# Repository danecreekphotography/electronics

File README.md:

# electronics
Random electronics projects

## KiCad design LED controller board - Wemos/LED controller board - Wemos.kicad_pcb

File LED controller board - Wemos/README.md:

# LED Controller Board - Wemos D1 Mini

This is a simple board that adds a logic level shifter to the D4 and RX pins
of a Wemos D1 Mini. With +5V and Ground output pins as well it makes a handy
little board for controlling short runs of LED light strips that don't require a
big external power supply.

## Schematic

A [printable version of the schematic](schematic.pdf) is available in PDF format.

## Bill of Materials

| Symbol | Description                                  | Quantity | Source                                                                                                         | Notes                                                                                                            |
| ------ | -------------------------------------------- | -------- | -------------------------------------------------------------------------------------------------------------- | ---------------------------------------------------------------------------------------------------------------- |
| C1     | 10 uF ceramic capacitor                      | 1        | [DigiKey](https://www.digikey.com/product-detail/en/tdk-corporation/FG16X7R1E106KRT06/445-173156-1-ND/5811761) | 2.5mm lead spacing                                                                                               |
| C2     | 0.1 uF ceramic capacitor                     | 1        | [DigiKey](https://www.digikey.com/product-detail/en/kemet/C322C104M5U5TA/399-4331-ND/818107)                   | 5mm lead spacing                                                                                                 |
| J1     | Molex KK male two pin right angle connector  | 1        | [DigiKey](https://www.digikey.com/product-detail/en/molex/1718570002/WM10157-ND/4423113)                       |                                                                                                                  |
| J2     | 1x8 2.54mm female pin header                 | 1        |                                                                                                                | This comes with the Wemos D1 Mini                                                                                |
| J3     | 1x8 2.54mm female pin header                 | 1        |                                                                                                                | This comes with the Wemos D1 Mini                                                                                |
| J4     | Molex KK male four pin right angle connector | 1        | [DigiKey](https://www.digikey.com/product-detail/en/molex/1718570004/WM10159-ND/4423115)                       |                                                                                                                  |
| U1     | Wemos D1 Mini                                | 1        | [Amazon](https://www.amazon.com/gp/product/B076F52NQD)                                                         | Header pins come with this set from Amazon so there is no need to buy additional headers to solder to the board. |
| U2     | TI CD40109BPWR unidirectional level shifter  | 1        | [DigiKey](https://www.digikey.com/product-detail/en/texas-instruments/CD40109BPWR/296-12163-1-ND/412005)       |                                                                                                                  |

## Ordering the PCB

The PCB can easily be [ordered from PCBWay](https://www.pcbway.com/project/shareproject/LED_Controller_Board___Wemos_D1_Mini.html). They're cheap, great quality, and arrive quickly. The default settings PCBWay applies to the board are perfect. All you have to
do is pick your favourite solder mask colour!

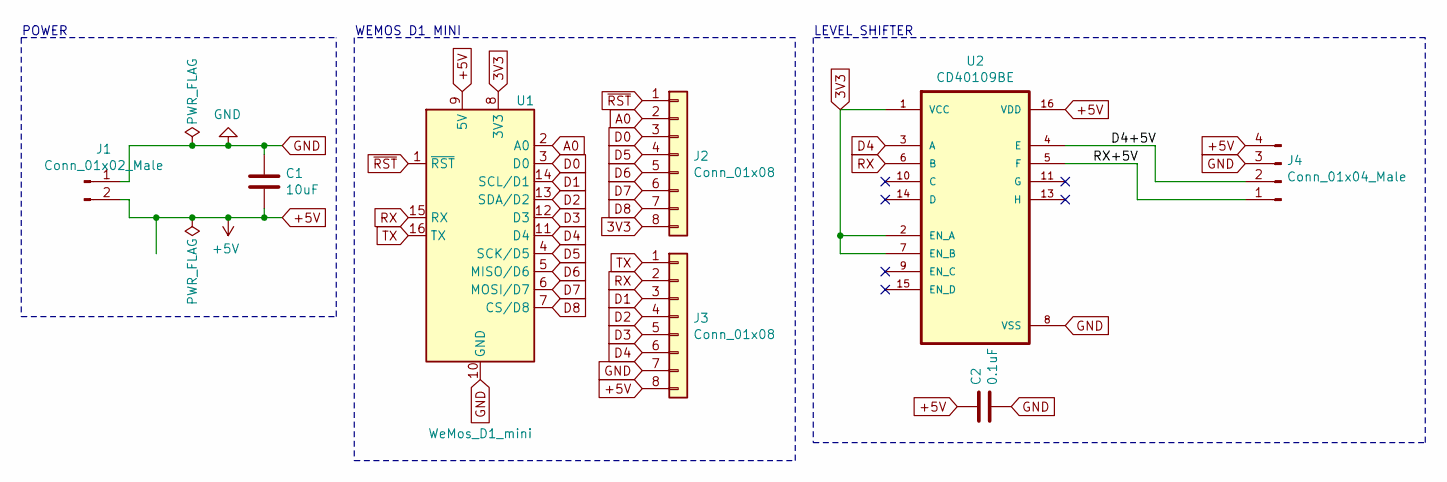
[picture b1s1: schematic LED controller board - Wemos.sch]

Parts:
C1: 10uF; C_Disc_D5.0mm_W2.5mm_P2.50mm
C2: 0.1uF; C_Disc_D5.0mm_W2.5mm_P5.00mm
J1: Conn_01x02_Male; Molex_KK-254_AE-6410-02A_1x02_P2.54mm_Horizontal
J2, J3: Conn_01x08; PinHeader_1x08_P2.54mm_Vertical
J4: Conn_01x04_Male; Molex_KK-254_AE-6410-04A_1x04_P2.54mm_Horizontal
U1: WeMos_D1_mini; WEMOS_D1_mini_light
U2: CD40109BE; 16TSSOP

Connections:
3V3: J2.8, U1.8 (3V3), U2.1 (VCC), U2.2 (EN_A), U2.7 (EN_B)
+5V: C1.2, C2.1, J1.2, J3.8, J4.4, U1.9 (5V), U2.16 (VDD)
/D4+5V: J4.2, U2.4 (E)
/RX+5V: J4.1, U2.5 (F)
A0: J2.2, U1.2 (A0)
D0: J2.3, U1.3 (D0)
D1: J3.3, U1.14 (SCL/D1)
D2: J3.4, U1.13 (SDA/D2)
D3: J3.5, U1.12 (D3)
D4: J3.6, U1.11 (D4), U2.3 (A)
D5: J2.4, U1.4 (SCK/D5)
D6: J2.5, U1.5 (MISO/D6)
D7: J2.6, U1.6 (MOSI/D7)
D8: J2.7, U1.7 (CS/D8)
GND: C1.1, C2.2, J1.1, J3.7, J4.3, U1.10 (GND), U2.8 (VSS)
RX: J3.2, U1.15 (RX), U2.6 (B)
TX: J3.1, U1.16 (TX)
~RST: J2.1, U1.1 (~RST)

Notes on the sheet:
POWER
WEMOS D1 MINI
LEVEL SHIFTER

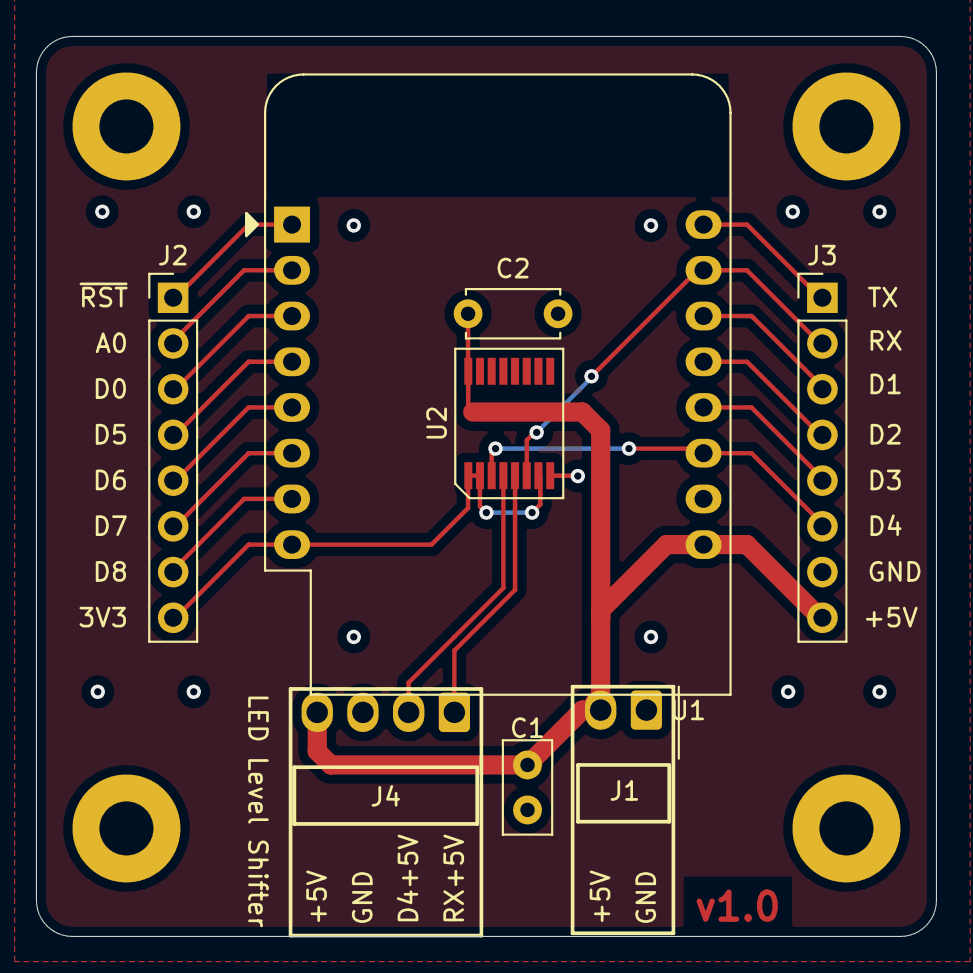
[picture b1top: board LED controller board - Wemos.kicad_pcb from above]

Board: 2 copper layers, 50.0 x 50.0 mm, 8 parts (0 on the bottom side), 18 nets.

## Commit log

2020-07-19 LED controller board - Wemos
2020-07-19 Readme and schematics
2020-07-19 Update readme with PCBWay link

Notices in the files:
LED controller board - Wemos/LED controller board - Wemos.sch:
Licensed: MIT License
